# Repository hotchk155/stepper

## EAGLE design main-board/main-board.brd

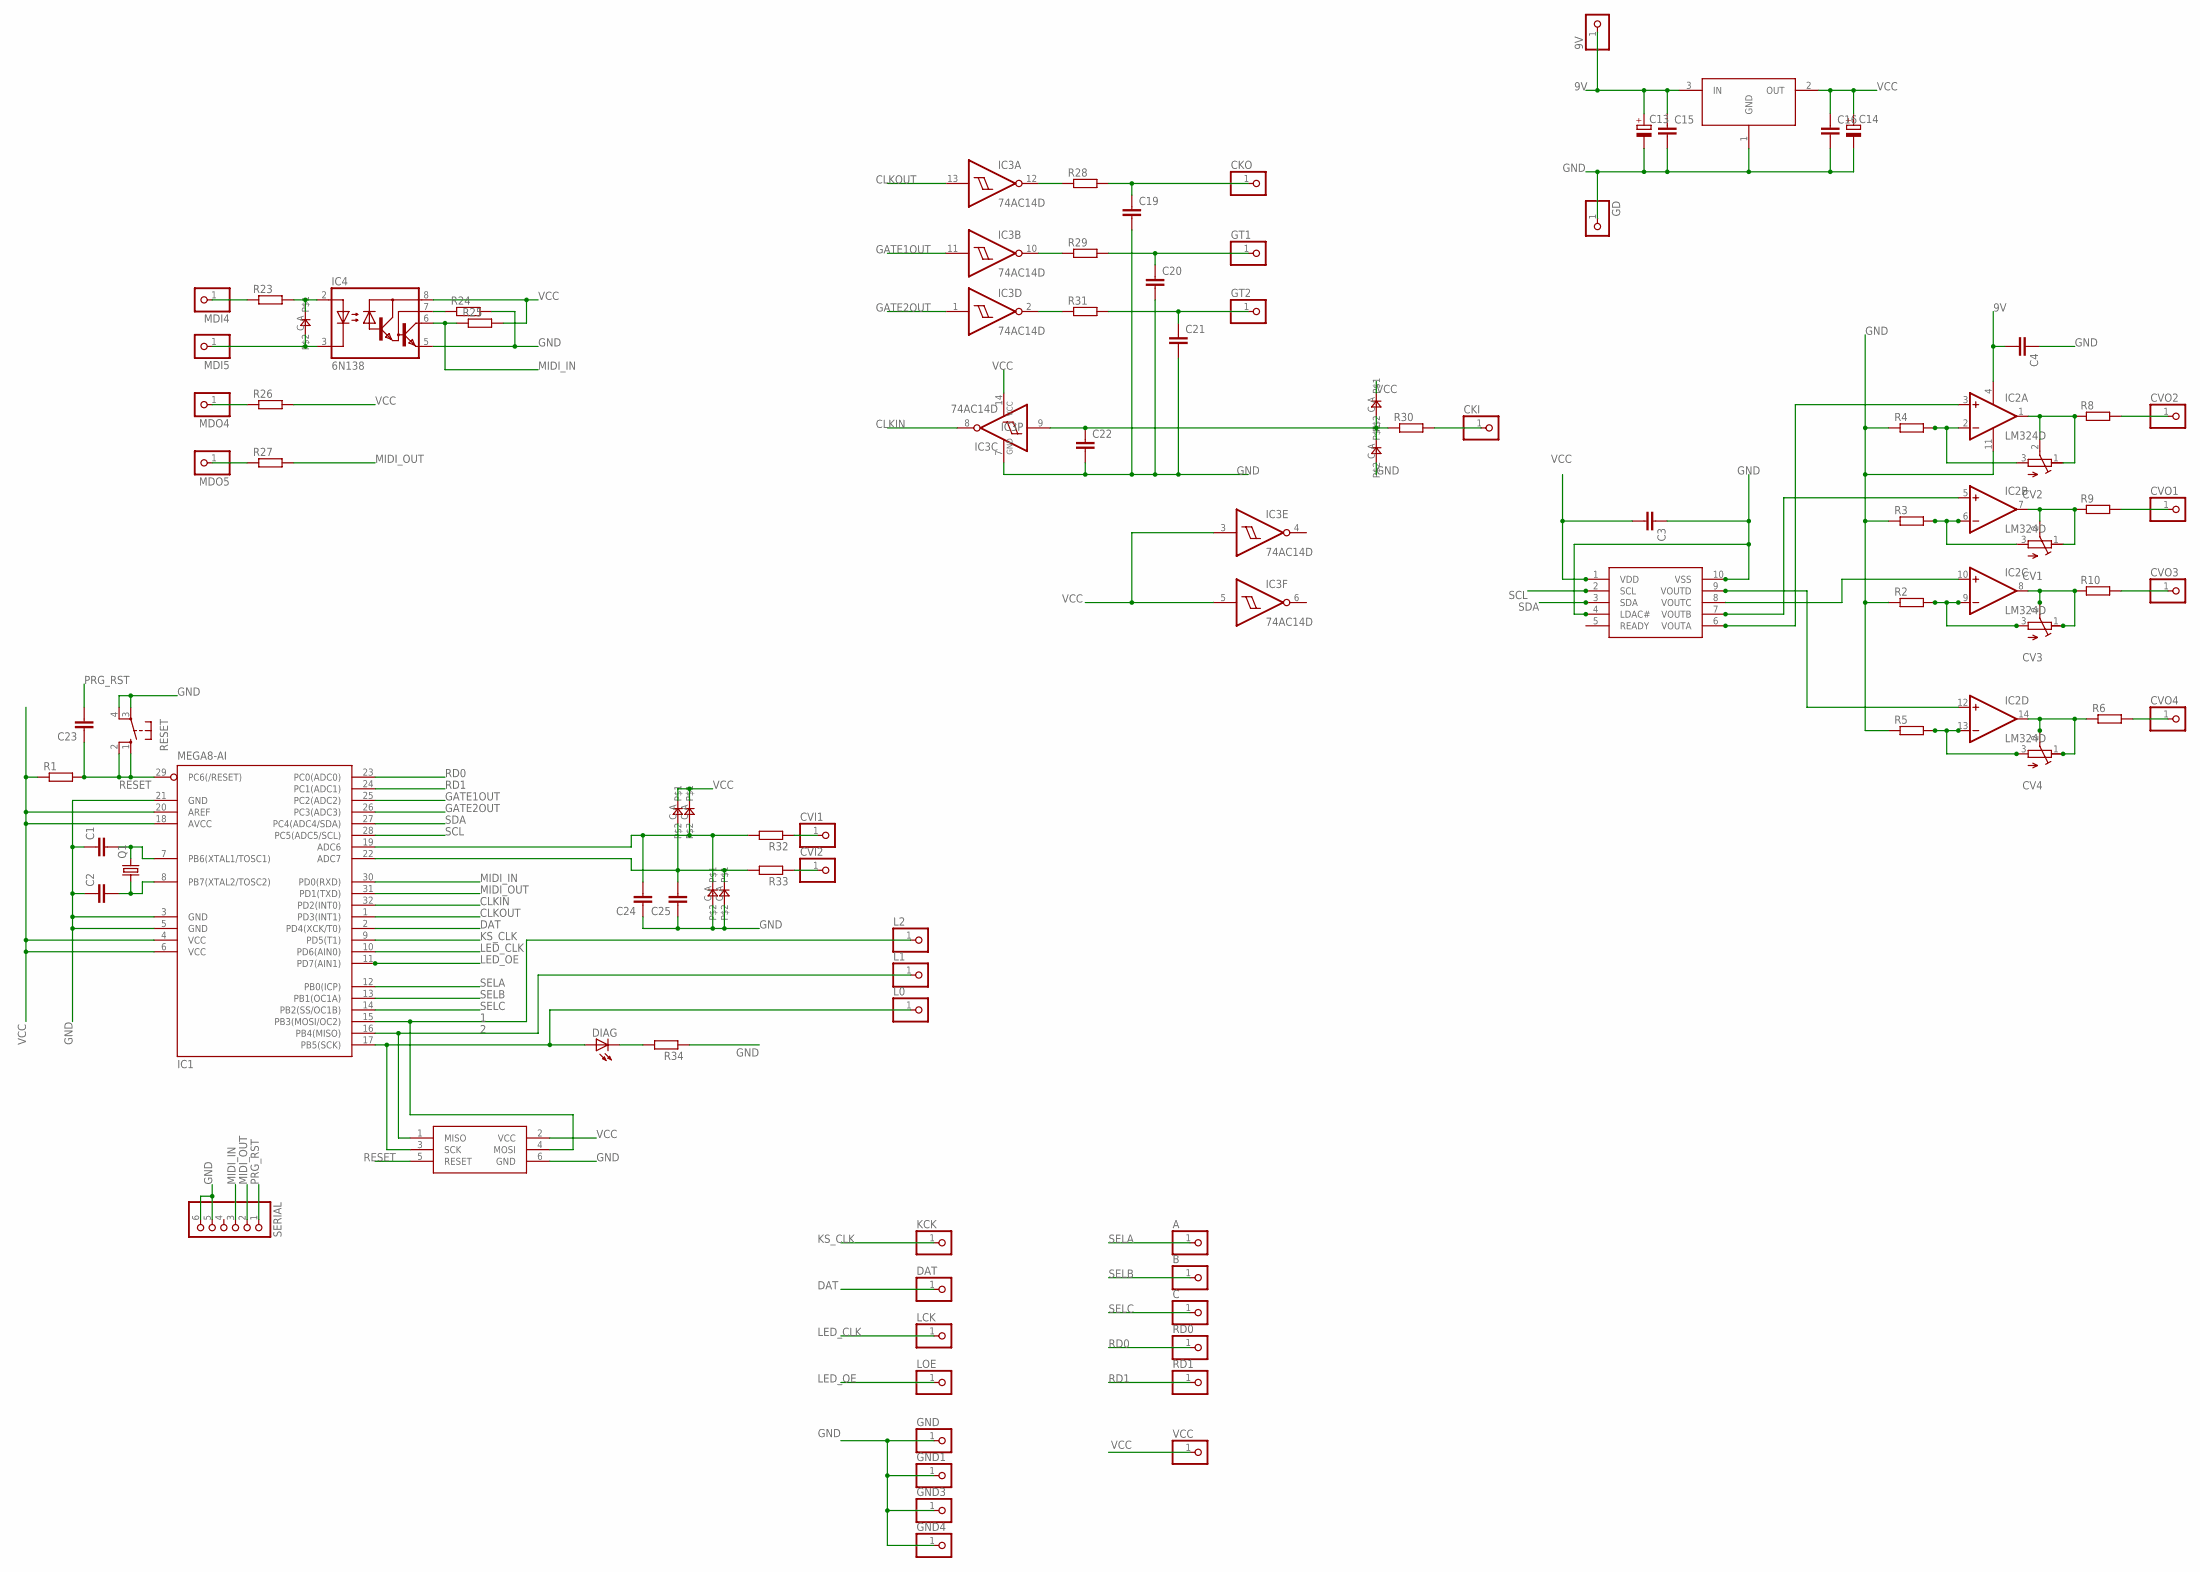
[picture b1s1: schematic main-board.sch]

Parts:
9V: PINHD-1X1; 1X01
A: PINHD-1X1; 1X01
B: PINHD-1X1; 1X01
C: PINHD-1X1; 1X01
C1, C2, C3, C4, C15, C16, C19, C20, C21, C22, C23, C24, C25: C-EUC0805; C0805
C13, C14: CPOL-EUE2-5; E2-5
CKI: PINHD-1X1; 1X01
CKO: PINHD-1X1; 1X01
CV1, CV2, CV3, CV4: R-TRIMM3006P; RTRIM3006P
CVI1, CVI2: PINHD-1X1; 1X01
CVO1, CVO2, CVO3, CVO4: PINHD-1X1; 1X01
D1, D2, D3, D4, D5, D6, D7: 0805DIODE
DAT: PINHD-1X1; 1X01
DIAG: LED3MM
GD: PINHD-1X1; 1X01
GND, GND1, GND3, GND4: PINHD-1X1; 1X01
GT1, GT2: PINHD-1X1; 1X01
IC1: MEGA8-AI; TQFP32-08
IC2: LM324D; SO14
IC3: 74AC14D; SO14
IC4: 6N138; DIL08
IC5: MCP4728_QUAD_DAC; MSOP10
ICSP: TAG_CONN_AVR; TC2030-MCP-NL
KCK: PINHD-1X1; 1X01
L0, L1, L2: PINHD-1X1; 1X01
LCK: PINHD-1X1; 1X01
LOE: PINHD-1X1; 1X01
MDI4, MDI5: PINHD-1X1; 1X01
MDO4, MDO5: PINHD-1X1; 1X01
Q1: CRYSTALHC49S; HC49/S
R1, R2, R3, R4, R5, R6, R8, R9, R10, R23, R24, R25, R26, R27, R28, R29, R30, R31, R32, R33, R34: R-EU_R0805; R0805
RD0, RD1: PINHD-1X1; 1X01
REG1: LD1086; DPACK
RESET: 10-XX; B3F-10XX
SERIAL: PINHD-1X6; 1X06
VCC: PINHD-1X1; 1X01

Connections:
1: IC1.15 (PB3(MOSI/OC2)), ICSP.4 (MOSI), L2.1
2: IC1.16 (PB4(MISO)), ICSP.1 (MISO), L1.1
3: DIAG.A, IC1.17 (PB5(SCK)), ICSP.3 (SCK), L0.1
9V: 9V.1, C4.2, C13.+, C15.1, IC2.4 (V+), REG1.3 (IN)
CLKIN: IC1.32 (PD2(INT0)), IC3.8 (O)
CLKOUT: IC1.1 (PD3(INT1)), IC3.13 (I)
CV1: CVO2.1, R8.2
DAT: DAT.1, IC1.2 (PD4(XCK/T0))
GATE1OUT: IC1.25 (PC2(ADC2)), IC3.11 (I)
GATE2OUT: IC1.26 (PC3(ADC3)), IC3.1 (I)
GND: C1.1, C2.1, C3.1, C4.1, C13.-, C14.-, C15.2, C16.2, C19.2, C20.2, C21.2, C22.2, C24.1, C25.1, D2.C, D4.C, D6.C, GD.1, GND.1, GND1.1, GND3.1, GND4.1, IC1.3 (GND), IC1.5 (GND), IC1.21 (GND), IC2.11 (V-), IC3.7 (GND), IC4.5 (GND), IC5.4 (LDAC#), IC5.10 (VSS), ICSP.6 (GND), R2.1, R3.1, R4.1, R5.1, R24.2, R34.1, REG1.1 (GND), RESET.3, RESET.4 (P1), SERIAL.5, SERIAL.6
KS_CLK: IC1.9 (PD5(T1)), KCK.1
LED_CLK: IC1.10 (PD6(AIN0)), LCK.1
LED_OE: IC1.11 (PD7(AIN1)), LOE.1
MIDI_IN: IC1.30 (PD0(RXD)), IC4.6 (VO), R25.1, SERIAL.3
MIDI_OUT: IC1.31 (PD1(TXD)), R27.2, SERIAL.2
unnamed: C2.2, IC1.8 (PB7(XTAL2/TOSC2)), Q1.1
unnamed: C1.2, IC1.7 (PB6(XTAL1/TOSC1)), Q1.2
unnamed: C24.2, D2.A, D3.C, IC1.19 (ADC6), R32.2
unnamed: C25.2, D4.A, D5.C, IC1.22 (ADC7), R33.2
unnamed: CV3.1 (A), CV3.2 (S), IC2.8 (OUT), R10.1
unnamed: CV2.3 (E), IC2.2 (-IN), R4.2
unnamed: CV3.3 (E), IC2.9 (-IN), R2.2
unnamed: CV4.1 (A), CV4.2 (S), IC2.14 (OUT), R6.1
unnamed: CVO4.1, R6.2
unnamed: CV1.3 (E), IC2.6 (-IN), R3.2
unnamed: CV2.1 (A), CV2.2 (S), IC2.1 (OUT), R8.1
unnamed: CV1.1 (A), CV1.2 (S), IC2.7 (OUT), R9.1
unnamed: IC2.10 (+IN), IC5.8 (VOUTC)
unnamed: IC2.5 (+IN), IC5.7 (VOUTB)
unnamed: CV4.3 (E), IC2.13 (-IN), R5.2
unnamed: IC2.12 (+IN), IC5.9 (VOUTD)
unnamed: IC2.3 (+IN), IC5.6 (VOUTA)
unnamed: D1.C, IC4.3 (C), MDI5.1
unnamed: D1.A, IC4.2 (A), R23.2
unnamed: MDI4.1, R23.1
unnamed: IC4.7 (VB), R24.1
unnamed: MDO4.1, R26.1
unnamed: MDO5.1, R27.1
unnamed: C22.1, D6.A, D7.C, IC3.9 (I), R30.1
unnamed: IC3.10 (O), R29.1
unnamed: IC3.12 (O), R28.1
unnamed: C19.1, CKO.1, R28.2
unnamed: C20.1, GT1.1, R29.2
unnamed: CKI.1, R30.2
unnamed: IC3.2 (O), R31.1
unnamed: C21.1, GT2.1, R31.2
unnamed: CVI1.1, R32.1
unnamed: CVI2.1, R33.1
unnamed: DIAG.K (C), R34.2
unnamed: CVO3.1, R10.2
unnamed: CVO1.1, R9.2
PRG_RST: C23.2, SERIAL.1
RD0: IC1.23 (PC0(ADC0)), RD0.1
RD1: IC1.24 (PC1(ADC1)), RD1.1
RESET: C23.1, IC1.29 (PC6(/RESET)), ICSP.5 (RESET), R1.2, RESET.1 (S), RESET.2 (S1)
SCL: IC1.28 (PC5(ADC5/SCL)), IC5.2 (SCL)
SDA: IC1.27 (PC4(ADC4/SDA)), IC5.3 (SDA)
SELA: A.1, IC1.12 (PB0(ICP))
SELB: B.1, IC1.13 (PB1(OC1A))
SELC: C.1, IC1.14 (PB2(SS/OC1B))
VCC: C3.2, C14.+, C16.1, D3.A, D5.A, D7.A, IC1.4 (VCC), IC1.6 (VCC), IC1.18 (AVCC), IC1.20 (AREF), IC3.3 (I), IC3.5 (I), IC3.14 (VCC), IC4.8 (VCC), IC5.1 (VDD), ICSP.2 (VCC), R1.1, R25.2, R26.2, REG1.2 (OUT), VCC.1

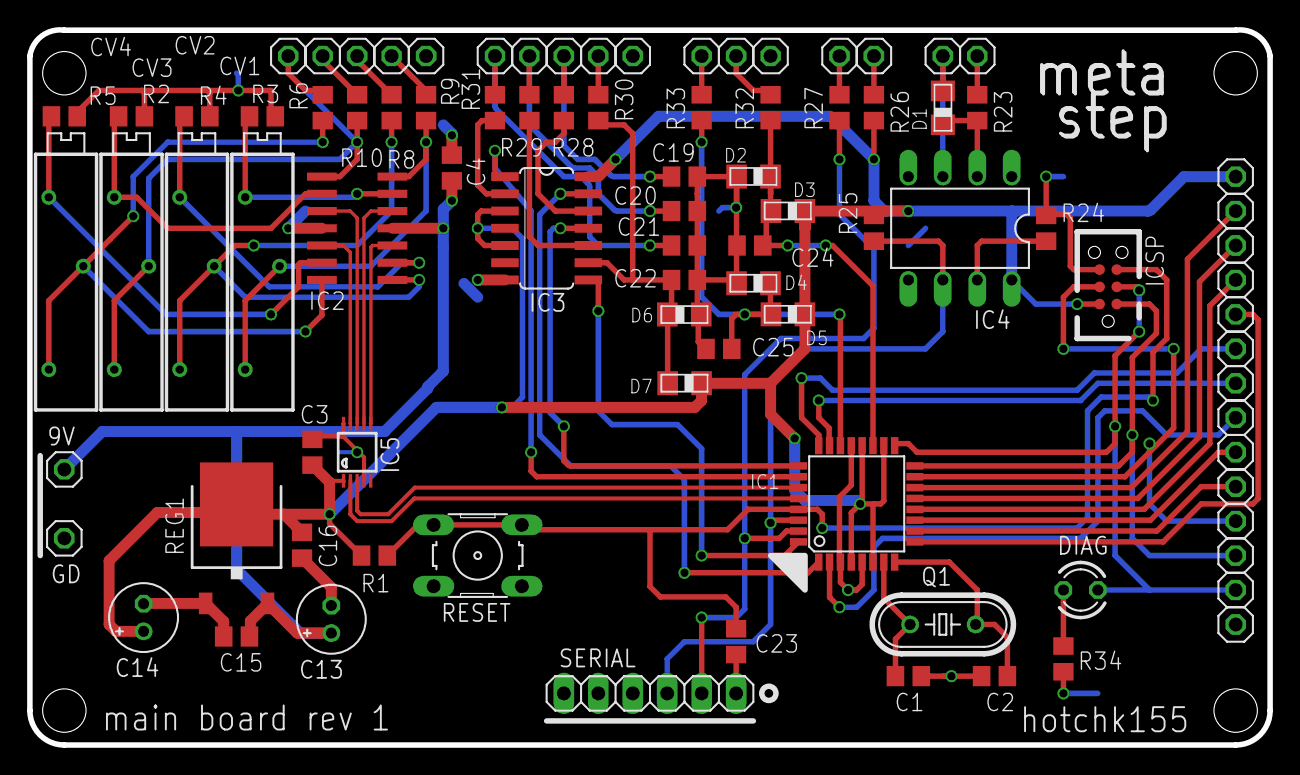
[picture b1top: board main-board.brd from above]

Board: 2 copper layers, 91.4 x 52.7 mm, 91 parts (0 on the bottom side), 62 nets.

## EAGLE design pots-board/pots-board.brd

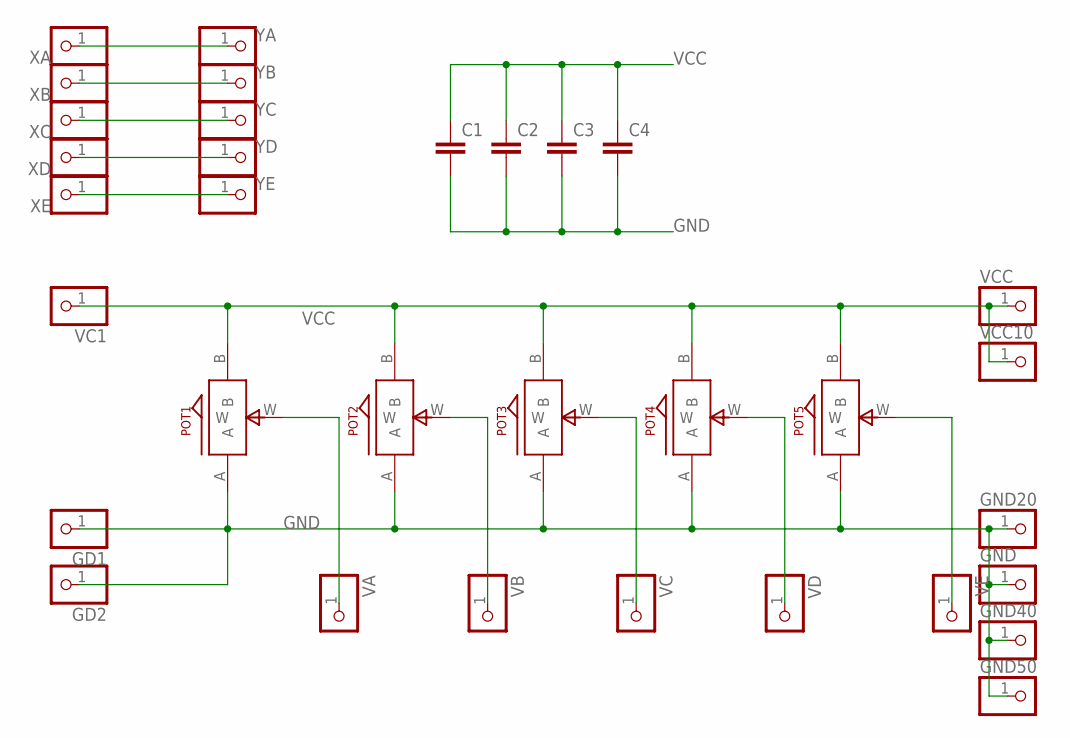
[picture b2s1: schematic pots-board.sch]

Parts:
C1, C2, C3, C4: C-EUC0805; C0805
GD1, GD2: PINHD-1X1; 1X01
GND, GND20, GND40, GND50: PINHD-1X1; 1X01
POT1, POT2, POT3, POT4, POT5: ALPS_POT_SMALL; SMALL_ALPS_POT
VA: PINHD-1X1; 1X01
VB: PINHD-1X1; 1X01
VC, VC1: PINHD-1X1; 1X01
VCC, VCC10: PINHD-1X1; 1X01
VD: PINHD-1X1; 1X01
VE: PINHD-1X1; 1X01
XA: PINHD-1X1; 1X01
XB: PINHD-1X1; 1X01
XC: PINHD-1X1; 1X01
XD: PINHD-1X1; 1X01
XE: PINHD-1X1; 1X01
YA: PINHD-1X1; 1X01
YB: PINHD-1X1; 1X01
YC: PINHD-1X1; 1X01
YD: PINHD-1X1; 1X01
YE: PINHD-1X1; 1X01

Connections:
GND: C1.2, C2.2, C3.2, C4.2, GD1.1, GD2.1, GND.1, GND20.1, GND40.1, GND50.1, POT1.A, POT2.A, POT3.A, POT4.A, POT5.A
unnamed: POT1.W, VA.1
unnamed: POT2.W, VB.1
unnamed: POT3.W, VC.1
unnamed: POT4.W, VD.1
unnamed: POT5.W, VE.1
unnamed: XA.1, YA.1
unnamed: XB.1, YB.1
unnamed: XC.1, YC.1
unnamed: XD.1, YD.1
unnamed: XE.1, YE.1
VCC: C1.1, C2.1, C3.1, C4.1, POT1.B, POT2.B, POT3.B, POT4.B, POT5.B, VC1.1, VCC.1, VCC10.1

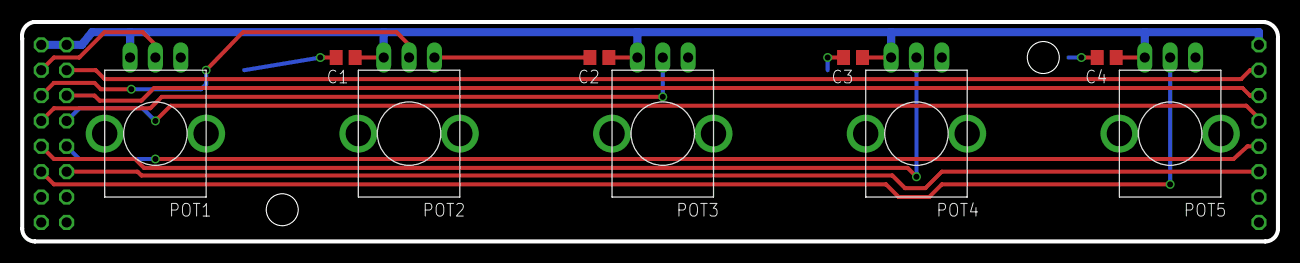
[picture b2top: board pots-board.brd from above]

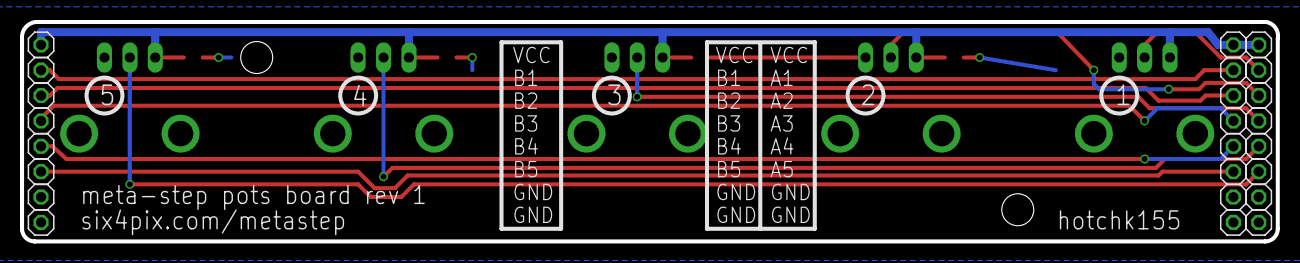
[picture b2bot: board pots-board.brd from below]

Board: 2 copper layers, 125.8 x 22.0 mm, 33 parts (24 on the bottom side), 12 nets.

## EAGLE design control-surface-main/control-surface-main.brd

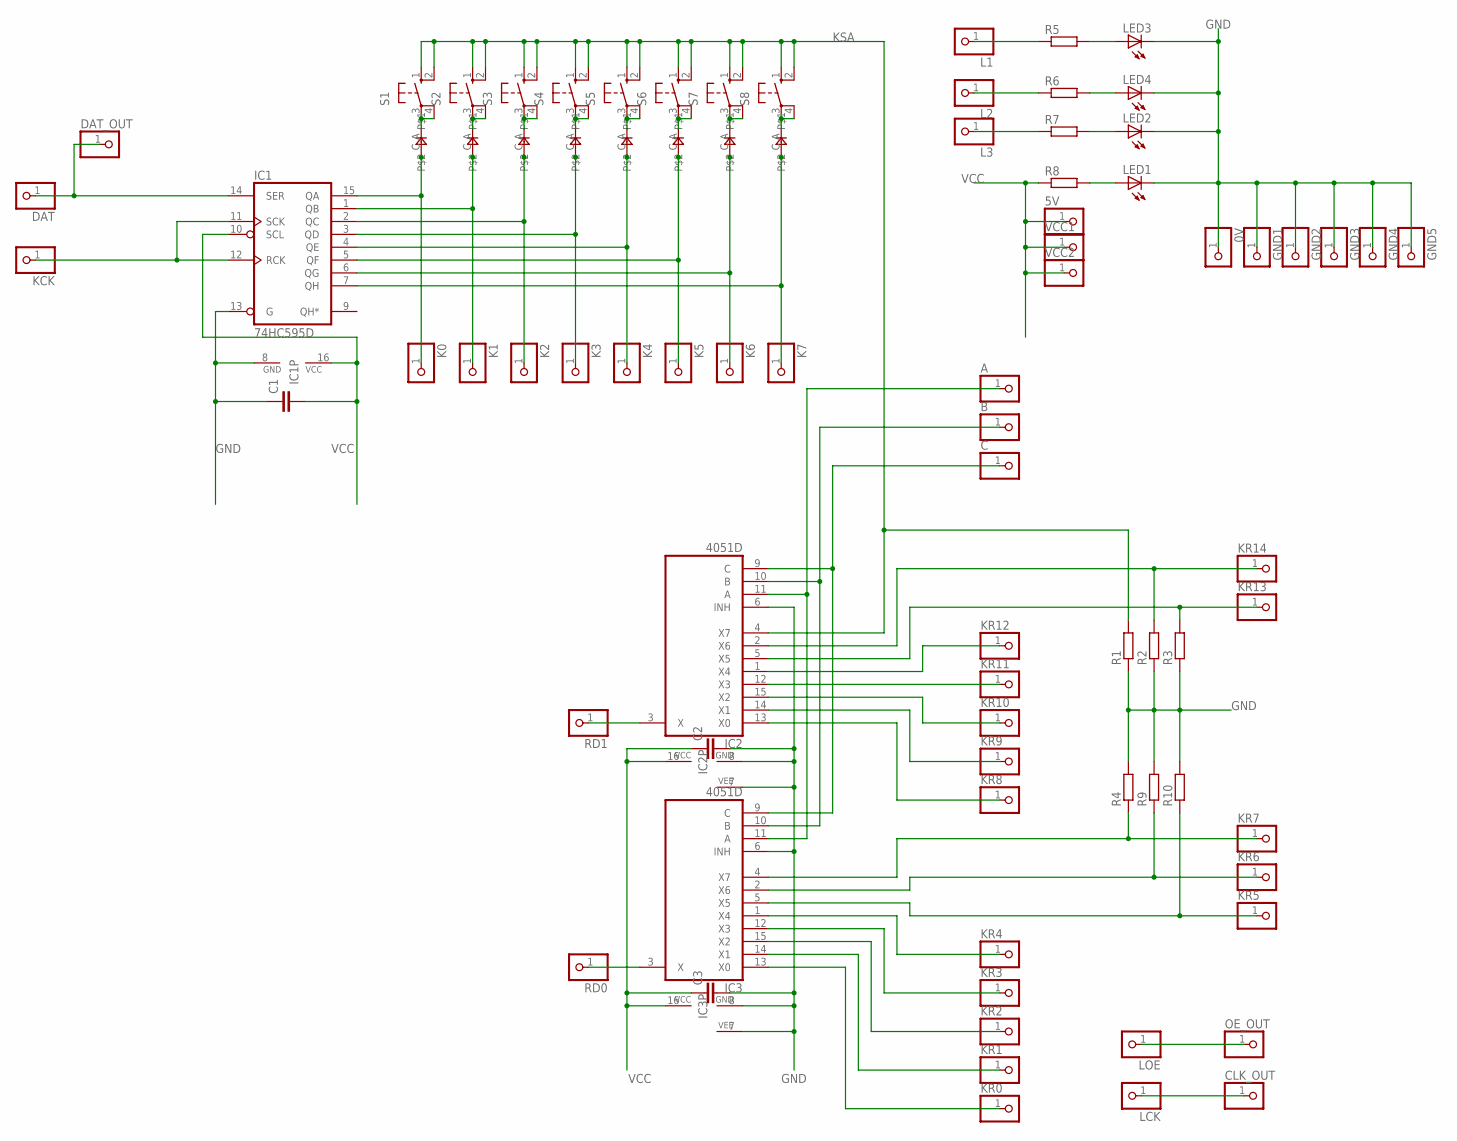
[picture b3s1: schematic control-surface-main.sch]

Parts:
0V, 5V: PINHD-1X1; 1X01
A: PINHD-1X1; 1X01
B: PINHD-1X1; 1X01
C: PINHD-1X1; 1X01
C1, C2, C3: C-EUC0805; C0805
CLK_OUT: PINHD-1X1; 1X01
D1, D2, D3, D4, D5, D6, D7, D8: 0805DIODE
DAT: PINHD-1X1; 1X01
DAT_OUT: PINHD-1X1; 1X01
GND1, GND2, GND3, GND4, GND5: PINHD-1X1; 1X01
IC1: 74HC595D; SO16
IC2, IC3: 4051D; SO16
K0, K1, K2, K3, K4, K5, K6, K7: PINHD-1X1; 1X01
KCK: PINHD-1X1; 1X01
KR0, KR1, KR2, KR3, KR4, KR5, KR6, KR7, KR8, KR9, KR10, KR11, KR12, KR13, KR14: PINHD-1X1; 1X01
L1, L2, L3: PINHD-1X1; 1X01
LCK: PINHD-1X1; 1X01
LED1, LED2, LED3, LED4: LED3MM
LOE: PINHD-1X1; 1X01
OE_OUT: PINHD-1X1; 1X01
R1, R2, R3, R4, R5, R6, R7, R8, R9, R10: R-EU_R0805; R0805
RD0, RD1: PINHD-1X1; 1X01
S1, S2, S3, S4, S5, S6, S7, S8: 40-XX; B3F-40XX
VCC1, VCC2: PINHD-1X1; 1X01

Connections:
DAT_IN: DAT.1, DAT_OUT.1, IC1.14 (SER)
GND: 0V.1, C1.1, C2.2, C3.2, GND1.1, GND2.1, GND3.1, GND4.1, GND5.1, IC1.8 (GND), IC1.13 (G), IC2.6 (INH), IC2.7 (VEE), IC2.8 (GND), IC3.6 (INH), IC3.7 (VEE), IC3.8 (GND), LED1.K (C), LED2.K (C), LED3.K (C), LED4.K (C), R1.1, R2.1, R3.1, R4.2, R9.2, R10.2
KSA: IC2.4 (X7), R1.2, S1.1 (S), S1.2 (S1), S2.1 (S), S2.2 (S1), S3.1 (S), S3.2 (S1), S4.1 (S), S4.2 (S1), S5.1 (S), S5.2 (S1), S6.1 (S), S6.2 (S1), S7.1 (S), S7.2 (S1), S8.1 (S), S8.2 (S1)
unnamed: D6.C, IC1.15 (QA), K0.1
unnamed: D6.A, S1.3, S1.4 (P1)
unnamed: D7.A, S2.3, S2.4 (P1)
unnamed: D8.A, S3.3, S3.4 (P1)
unnamed: D1.A, S4.3, S4.4 (P1)
unnamed: D2.A, S5.3, S5.4 (P1)
unnamed: D3.A, S6.3, S6.4 (P1)
unnamed: D4.A, S7.3, S7.4 (P1)
unnamed: D5.A, S8.3, S8.4 (P1)
unnamed: D7.C, IC1.1 (QB), K1.1
unnamed: D8.C, IC1.2 (QC), K2.1
unnamed: D1.C, IC1.3 (QD), K3.1
unnamed: D2.C, IC1.4 (QE), K4.1
unnamed: D3.C, IC1.5 (QF), K5.1
unnamed: D4.C, IC1.6 (QG), K6.1
unnamed: D5.C, IC1.7 (QH), K7.1
unnamed: C.1, IC2.9 (C), IC3.9 (C)
unnamed: B.1, IC2.10 (B), IC3.10 (B)
unnamed: IC1.11 (SCK), IC1.12 (RCK), KCK.1
unnamed: A.1, IC2.11 (A), IC3.11 (A)
unnamed: LOE.1, OE_OUT.1
unnamed: IC2.2 (X6), KR14.1, R2.2
unnamed: IC2.5 (X5), KR13.1, R3.2
unnamed: LED3.A, R5.2
unnamed: LED4.A, R6.2
unnamed: LED2.A, R7.2
unnamed: LED1.A, R8.2
unnamed: IC2.1 (X4), KR12.1
unnamed: L1.1, R5.1
unnamed: L2.1, R6.1
unnamed: L3.1, R7.1
unnamed: IC2.12 (X3), KR11.1
unnamed: IC2.15 (X2), KR10.1
unnamed: IC2.14 (X1), KR9.1
unnamed: IC2.13 (X0), KR8.1
unnamed: IC3.4 (X7), KR7.1, R4.1
unnamed: IC3.2 (X6), KR6.1, R9.1
unnamed: IC3.5 (X5), KR5.1, R10.1
unnamed: IC3.1 (X4), KR4.1
unnamed: IC3.12 (X3), KR3.1
unnamed: IC3.15 (X2), KR2.1
unnamed: IC3.14 (X1), KR1.1
unnamed: IC3.13 (X0), KR0.1
unnamed: IC3.3 (X), RD0.1
unnamed: IC2.3 (X), RD1.1
unnamed: CLK_OUT.1, LCK.1
VCC: 5V.1, C1.2, C2.1, C3.1, IC1.10 (SCL), IC1.16 (VCC), IC2.16 (VCC), IC3.16 (VCC), R8.1, VCC1.1, VCC2.1

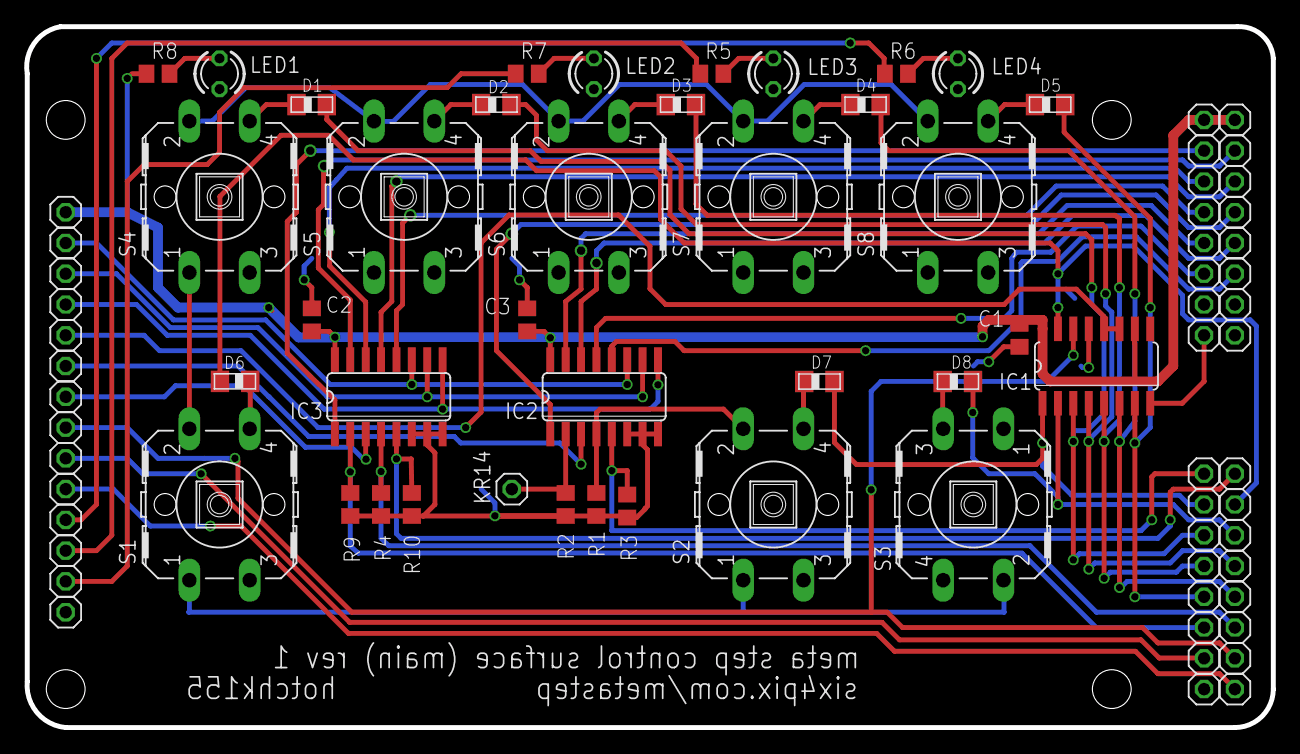
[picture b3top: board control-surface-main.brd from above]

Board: 2 copper layers, 102.9 x 57.9 mm, 83 parts (0 on the bottom side), 50 nets.

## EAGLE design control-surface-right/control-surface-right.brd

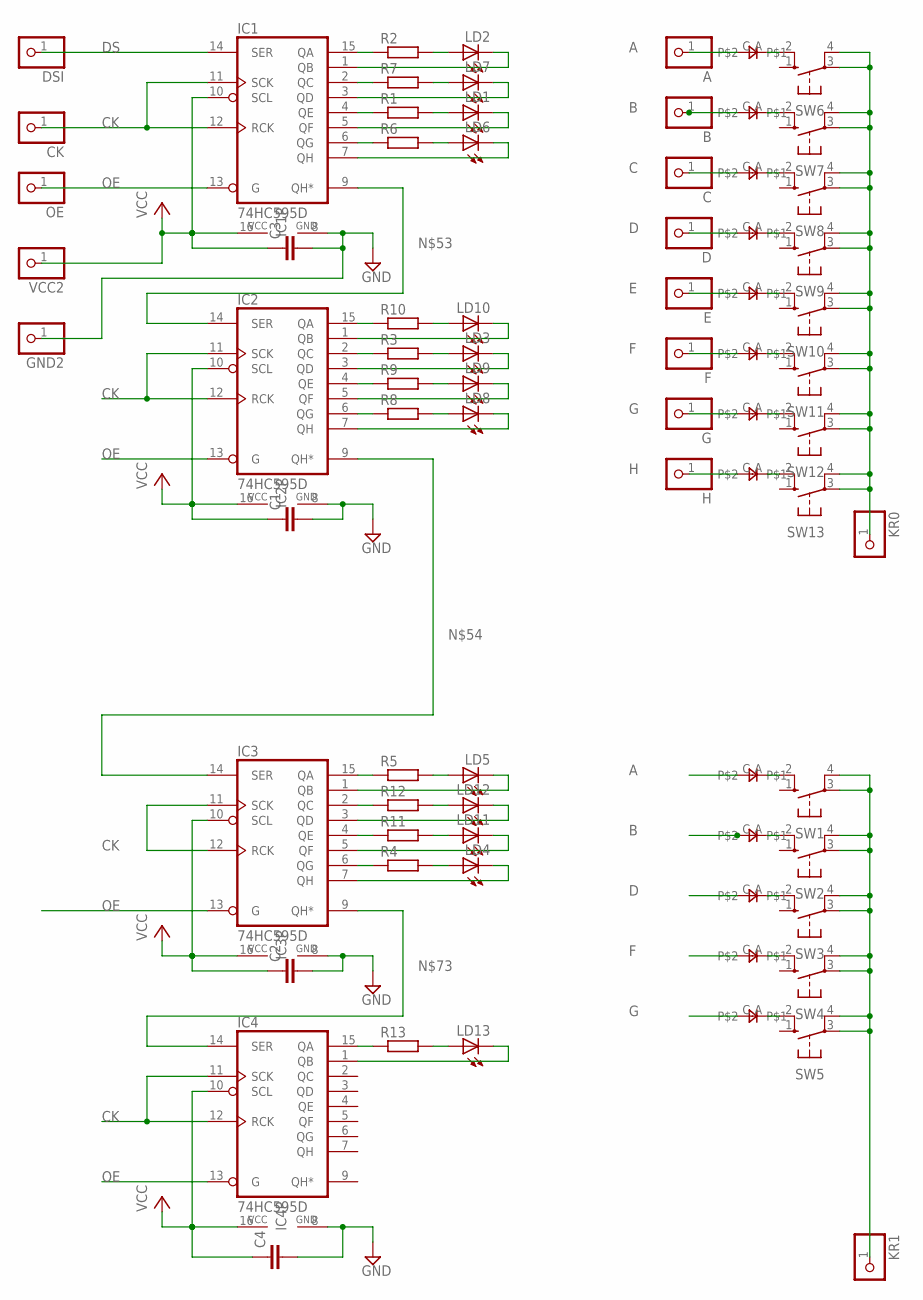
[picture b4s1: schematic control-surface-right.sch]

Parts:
A: PINHD-1X1; 1X01
B: PINHD-1X1; 1X01
C: PINHD-1X1; 1X01
C1, C2, C3, C4: C-EUC0805; C0805
CK: PINHD-1X1; 1X01
D: PINHD-1X1; 1X01
D1, D2, D3, D4, D5, D6, D7, D8, D9, D10, D11, D12, D13: 0805DIODE
DSI: PINHD-1X1; 1X01
E: PINHD-1X1; 1X01
F: PINHD-1X1; 1X01
G: PINHD-1X1; 1X01
GND2: PINHD-1X1; 1X01
H: PINHD-1X1; 1X01
IC1, IC2, IC3, IC4: 74HC595D; SO16
KR0, KR1: PINHD-1X1; 1X01
LD1, LD2, LD3, LD4, LD5, LD6, LD7, LD8, LD9, LD10, LD11, LD12, LD13: LED3MM
OE: PINHD-1X1; 1X01
R1, R2, R3, R4, R5, R6, R7, R8, R9, R10, R11, R12, R13: R-EU_R0805; R0805
SW1, SW2, SW3, SW4, SW5, SW6, SW7, SW8, SW9, SW10, SW11, SW12, SW13: 40-XX; B3F-40XX
VCC2: PINHD-1X1; 1X01

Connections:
A: A.1, D1.C, D6.C
B: B.1, D2.C, D7.C
C: C.1, D8.C
CK: CK.1, IC1.11 (SCK), IC1.12 (RCK), IC2.11 (SCK), IC2.12 (RCK), IC3.11 (SCK), IC3.12 (RCK), IC4.11 (SCK), IC4.12 (RCK)
D: D.1, D3.C, D9.C
DS: DSI.1, IC1.14 (SER)
E: D10.C, E.1
F: D4.C, D11.C, F.1
G: D5.C, D12.C, G.1
GND: C1.2, C2.2, C3.2, C4.2, GND2.1, IC1.8 (GND), IC2.8 (GND), IC3.8 (GND), IC4.8 (GND)
H: D13.C, H.1
unnamed: IC1.6 (QG), R6.1
unnamed: LD6.A, R6.2
unnamed: IC1.7 (QH), LD6.K (C)
unnamed: IC1.4 (QE), R1.1
unnamed: IC1.5 (QF), LD1.K (C)
unnamed: LD1.A, R1.2
unnamed: IC1.3 (QD), LD7.K (C)
unnamed: LD7.A, R7.2
unnamed: IC1.2 (QC), R7.1
unnamed: IC1.15 (QA), R2.1
unnamed: IC1.1 (QB), LD2.K (C)
unnamed: LD2.A, R2.2
unnamed: IC2.6 (QG), R8.1
unnamed: LD8.A, R8.2
unnamed: IC2.7 (QH), LD8.K (C)
unnamed: IC2.4 (QE), R9.1
unnamed: IC2.5 (QF), LD9.K (C)
unnamed: LD9.A, R9.2
unnamed: IC2.3 (QD), LD3.K (C)
unnamed: LD3.A, R3.2
unnamed: IC2.2 (QC), R3.1
unnamed: IC2.15 (QA), R10.1
unnamed: IC2.1 (QB), LD10.K (C)
unnamed: LD10.A, R10.2
unnamed: KR0.1, SW6.3, SW6.4 (P1), SW7.3, SW7.4 (P1), SW8.3, SW8.4 (P1), SW9.3, SW9.4 (P1), SW10.3, SW10.4 (P1), SW11.3, SW11.4 (P1), SW12.3, SW12.4 (P1), SW13.3, SW13.4 (P1)
unnamed: D13.A, SW13.2 (S1)
unnamed: D12.A, SW12.2 (S1)
unnamed: D11.A, SW11.2 (S1)
unnamed: D10.A, SW10.2 (S1)
unnamed: D9.A, SW9.2 (S1)
unnamed: D8.A, SW8.2 (S1)
unnamed: D7.A, SW7.2 (S1)
unnamed: D6.A, SW6.2 (S1)
unnamed: IC3.6 (QG), R4.1
unnamed: LD4.A, R4.2
unnamed: IC3.7 (QH), LD4.K (C)
unnamed: IC3.4 (QE), R11.1
unnamed: IC3.5 (QF), LD11.K (C)
unnamed: LD11.A, R11.2
unnamed: IC3.3 (QD), LD12.K (C)
unnamed: LD12.A, R12.2
unnamed: IC1.9 (QH*), IC2.14 (SER)
unnamed: IC2.9 (QH*), IC3.14 (SER)
unnamed: IC3.2 (QC), R12.1
unnamed: IC3.15 (QA), R5.1
unnamed: IC3.1 (QB), LD5.K (C)
unnamed: LD5.A, R5.2
unnamed: IC4.15 (QA), R13.1
unnamed: IC4.1 (QB), LD13.K (C)
unnamed: LD13.A, R13.2
unnamed: IC3.9 (QH*), IC4.14 (SER)
unnamed: KR1.1, SW1.3, SW1.4 (P1), SW2.3, SW2.4 (P1), SW3.3, SW3.4 (P1), SW4.3, SW4.4 (P1), SW5.3, SW5.4 (P1)
unnamed: D5.A, SW5.2 (S1)
unnamed: D4.A, SW4.2 (S1)
unnamed: D3.A, SW3.2 (S1)
unnamed: D2.A, SW2.2 (S1)
unnamed: D1.A, SW1.2 (S1)
OE: IC1.13 (G), IC2.13 (G), IC3.13 (G), IC4.13 (G), OE.1
VCC: C1.1, C2.1, C3.1, C4.1, IC1.10 (SCL), IC1.16 (VCC), IC2.10 (SCL), IC2.16 (VCC), IC3.10 (SCL), IC3.16 (VCC), IC4.10 (SCL), IC4.16 (VCC), VCC2.1

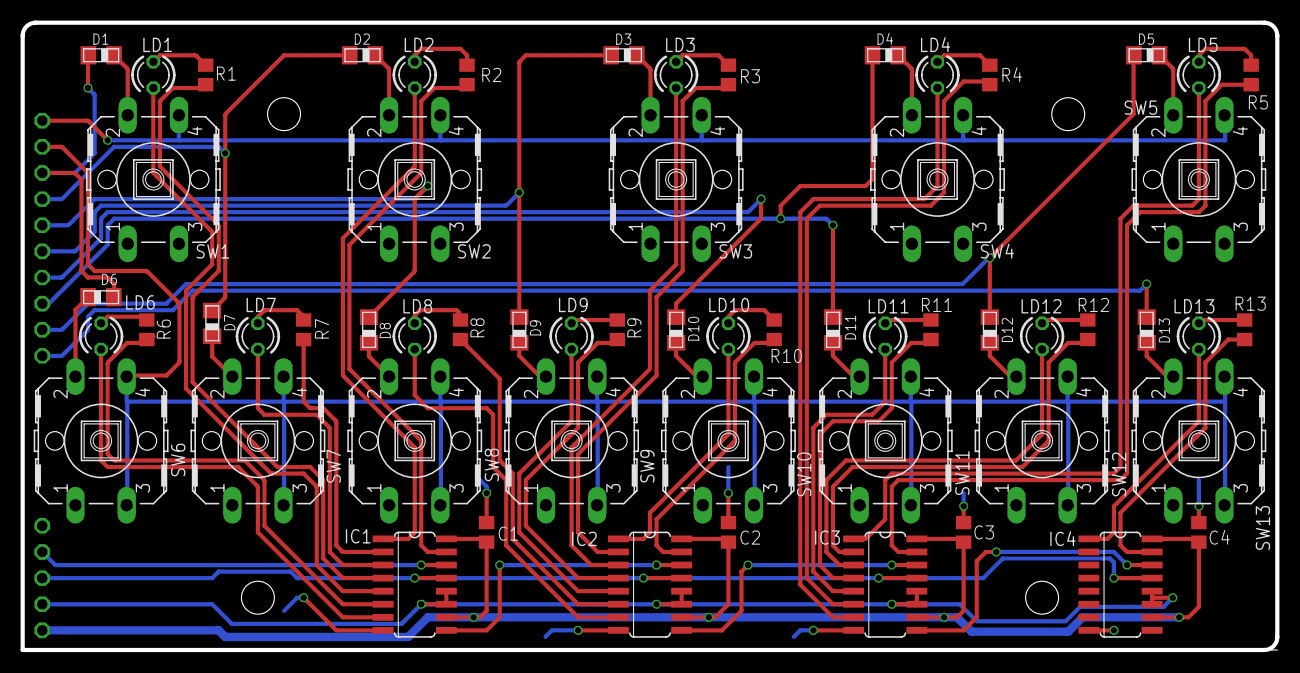
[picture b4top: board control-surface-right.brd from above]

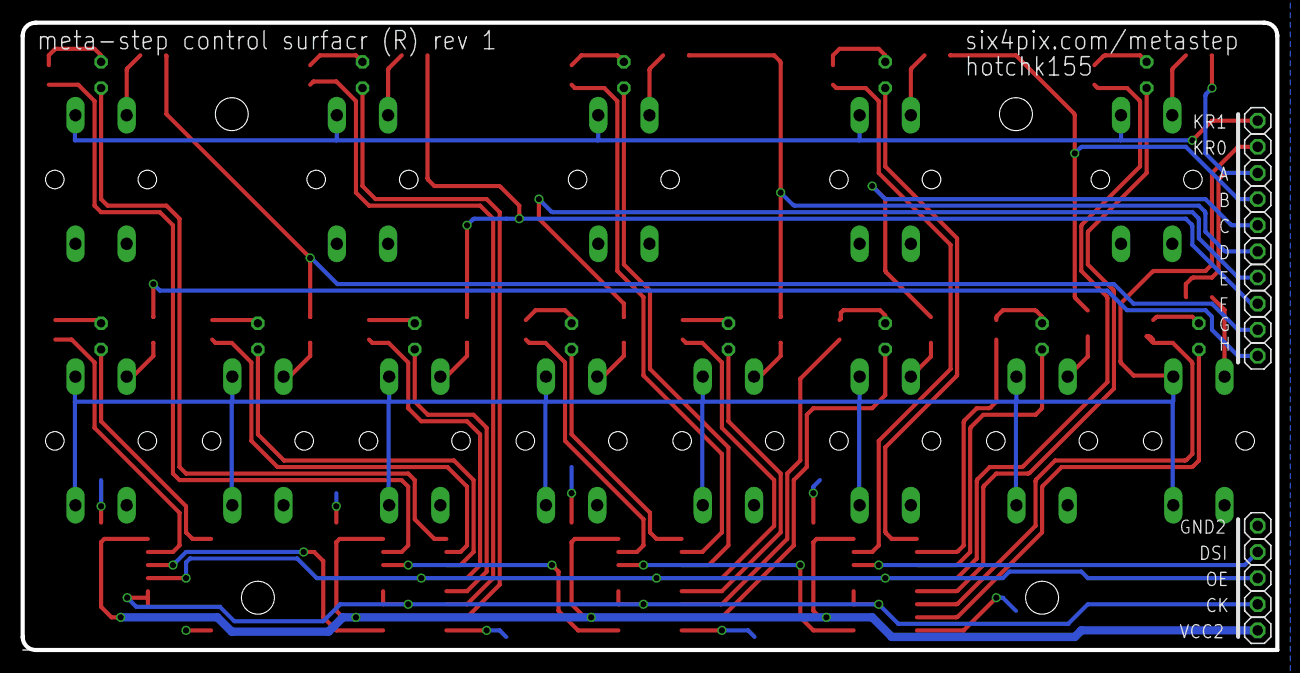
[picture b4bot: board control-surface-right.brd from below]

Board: 2 copper layers, 121.9 x 61.0 mm, 75 parts (15 on the bottom side), 70 nets.

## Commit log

2015-06-07 :octocat: Added .gitattributes
2015-08-30 mods
2015-08-30 reverse order
2015-09-02 in progress
2015-09-02 in work
2015-09-03 mode mods
2015-09-03 stuff
2015-09-08 more stff
2015-10-12 move leds
2015-10-12 rotate pots

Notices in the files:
parts and their libraries:
jasons_stuff: ©2009 ROFA.cz - modified and updated by Robert Darlington ‹rdarlington@gmail.com›
